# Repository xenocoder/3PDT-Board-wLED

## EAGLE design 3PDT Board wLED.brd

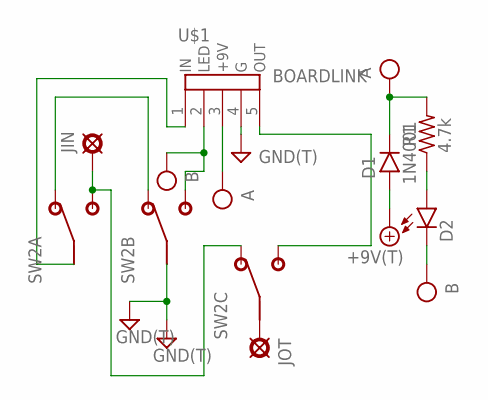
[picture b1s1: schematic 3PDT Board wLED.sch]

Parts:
+9V: +9V(T); SQUARE
D1: 1N4001; DO41-3
D2: LED3MM
G: GND(T); SQUARE
JIG: GND(T); SQUARE
JIN: PAD; SQUARE
JOG: GND(T); SQUARE
JOT: PAD; SQUARE
R1: 4.7k; R0207/3
SW2: 3PDT
U$1: BOARDLINK

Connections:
+9V: +9V.1, D1.A
A: D1.C, R1.2, U$1.3 (+9V)
B: D2.K (C), SW2.B3 (3), U$1.2 (LED)
GND: G.1, JIG.1, JOG.1, SW2.B2 (2), U$1.4 (G)
unnamed: JOT.1, SW2.C2 (2)
unnamed: SW2.A1 (1), SW2.B1 (1)
unnamed: JIN.1, SW2.A3 (3), SW2.C1 (1)
unnamed: SW2.A2 (2), U$1.1 (IN)
unnamed: SW2.C3 (3), U$1.5 (OUT)
unnamed: D2.A, R1.1

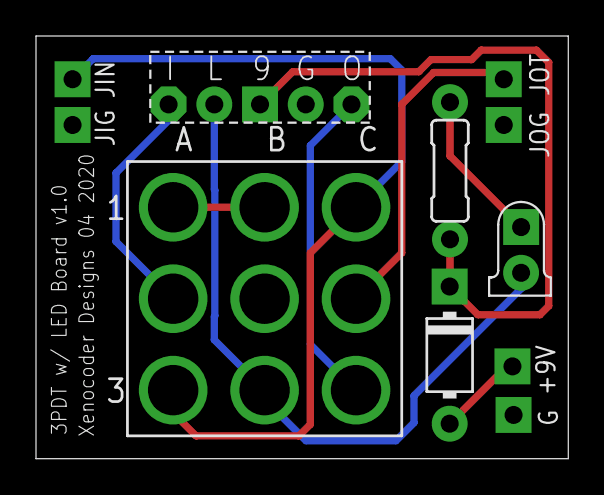
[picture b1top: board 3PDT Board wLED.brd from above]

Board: 2 copper layers, 29.6 x 23.5 mm, 11 parts (0 on the bottom side), 10 nets.

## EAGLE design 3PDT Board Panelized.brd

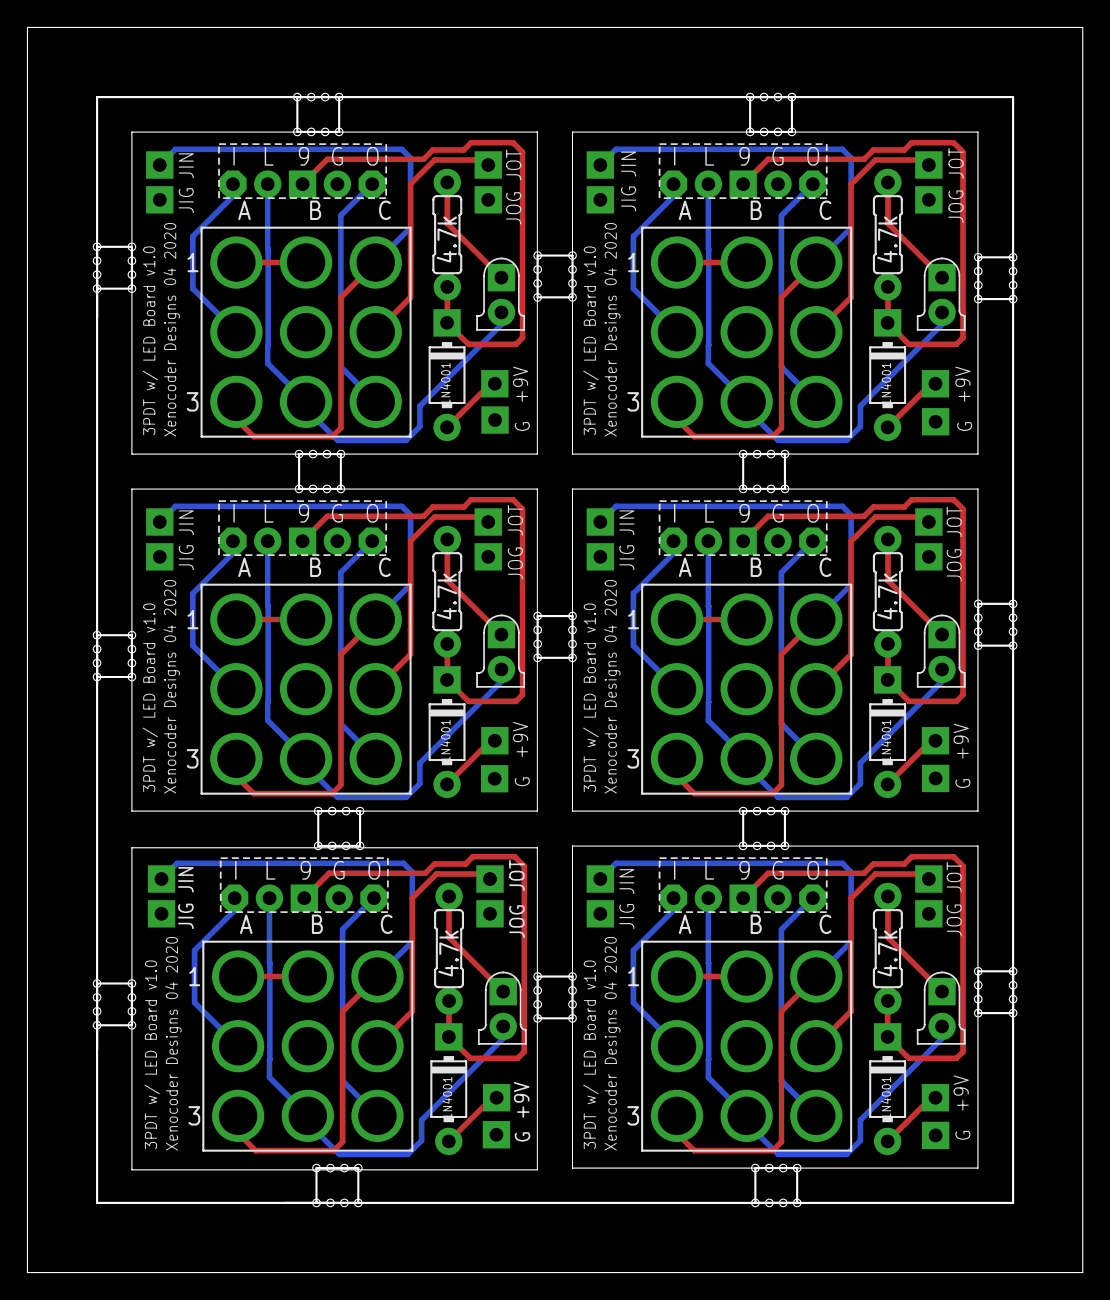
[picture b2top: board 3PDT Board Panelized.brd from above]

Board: 2 copper layers, 76.8 x 90.7 mm, 66 parts (0 on the bottom side), 60 nets.

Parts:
+9V, +9V1, +9V2, +9V3, +9V4, +9V5: +9V(T); SQUARE
D1, D3, D5, D7, D9, D11: 1N4001; DO41-3
D2, D4, D6, D8, D10, D12: LED3MM
G, G2, G3, G4, G5: GND(T); SQUARE
G1: G; SQUARE
JIG, JIG1, JIG2, JIG3, JIG4, JIG5: GND(T); SQUARE
JIN, JIN1, JIN2, JIN3, JIN4, JIN5: SQUARE
JOG, JOG1, JOG2, JOG3, JOG4, JOG5: GND(T); SQUARE
JOT, JOT1, JOT2, JOT3, JOT4, JOT5: SQUARE
R1, R2, R3, R4, R5, R6: 4.7k; R0207/3
SW1, SW2, SW3, SW4, SW5, SW6: 3PDT
U$1, U$2, U$3, U$4, U$5, U$6: BOARDLINK

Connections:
+9V: +9V.1, D1.A
+9V1: +9V1.1, D3.A
+9V2: +9V2.1, D5.A
+9V3: +9V3.1, D7.A
+9V4: +9V4.1, D9.A
+9V5: +9V5.1, D11.A
A: D1.C, R1.2, U$1.3
A1: D3.C, R2.2, U$2.3
A2: D5.C, R3.2, U$3.3
A3: D7.C, R4.2, U$4.3
A4: D9.C, R5.2, U$5.3
A5: D11.C, R6.2, U$6.3
B: D2.K, SW2.B3, U$1.2
B1: D4.K, SW1.B3, U$2.2
B2: D6.K, SW3.B3, U$3.2
B3: D8.K, SW4.B3, U$4.2
B4: D10.K, SW5.B3, U$5.2
B5: D12.K, SW6.B3, U$6.2
GND: G.1, JIG.1, JOG.1, SW2.B2, U$1.4
GND1: G1.1, JIG1.1, JOG1.1, SW1.B2, U$2.4
GND2: G2.1, JIG2.1, JOG2.1, SW3.B2, U$3.4
GND3: G3.1, JIG3.1, JOG3.1, SW4.B2, U$4.4
GND4: G4.1, JIG4.1, JOG4.1, SW5.B2, U$5.4
GND5: G5.1, JIG5.1, JOG5.1, SW6.B2, U$6.4
unnamed: JOT1.1, SW1.C2
unnamed: JOT.1, SW2.C2
unnamed: SW2.A1, SW2.B1
unnamed: JIN.1, SW2.A3, SW2.C1
unnamed: SW2.A2, U$1.1
unnamed: SW2.C3, U$1.5
unnamed: D2.A, R1.1
unnamed: JIN1.1, SW1.A3, SW1.C1
unnamed: SW1.A1, SW1.B1
unnamed: SW1.A2, U$2.1
unnamed: SW1.C3, U$2.5
unnamed: D4.A, R2.1
unnamed: JOT2.1, SW3.C2
unnamed: JIN2.1, SW3.A3, SW3.C1
unnamed: SW3.A1, SW3.B1
unnamed: SW3.A2, U$3.1
unnamed: SW3.C3, U$3.5
unnamed: D6.A, R3.1
unnamed: JOT3.1, SW4.C2
unnamed: JIN3.1, SW4.A3, SW4.C1
unnamed: SW4.A1, SW4.B1
unnamed: SW4.A2, U$4.1
unnamed: SW4.C3, U$4.5
unnamed: D8.A, R4.1
unnamed: JOT4.1, SW5.C2
unnamed: JIN4.1, SW5.A3, SW5.C1
unnamed: SW5.A1, SW5.B1
unnamed: SW5.A2, U$5.1
unnamed: SW5.C3, U$5.5
unnamed: D10.A, R5.1
unnamed: JOT5.1, SW6.C2
unnamed: JIN5.1, SW6.A3, SW6.C1
unnamed: SW6.A1, SW6.B1
unnamed: SW6.A2, U$6.1
unnamed: SW6.C3, U$6.5
unnamed: D12.A, R6.1

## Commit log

2020-04-29 Working on panelization
2020-05-17 Commit Seeed board and backup files
